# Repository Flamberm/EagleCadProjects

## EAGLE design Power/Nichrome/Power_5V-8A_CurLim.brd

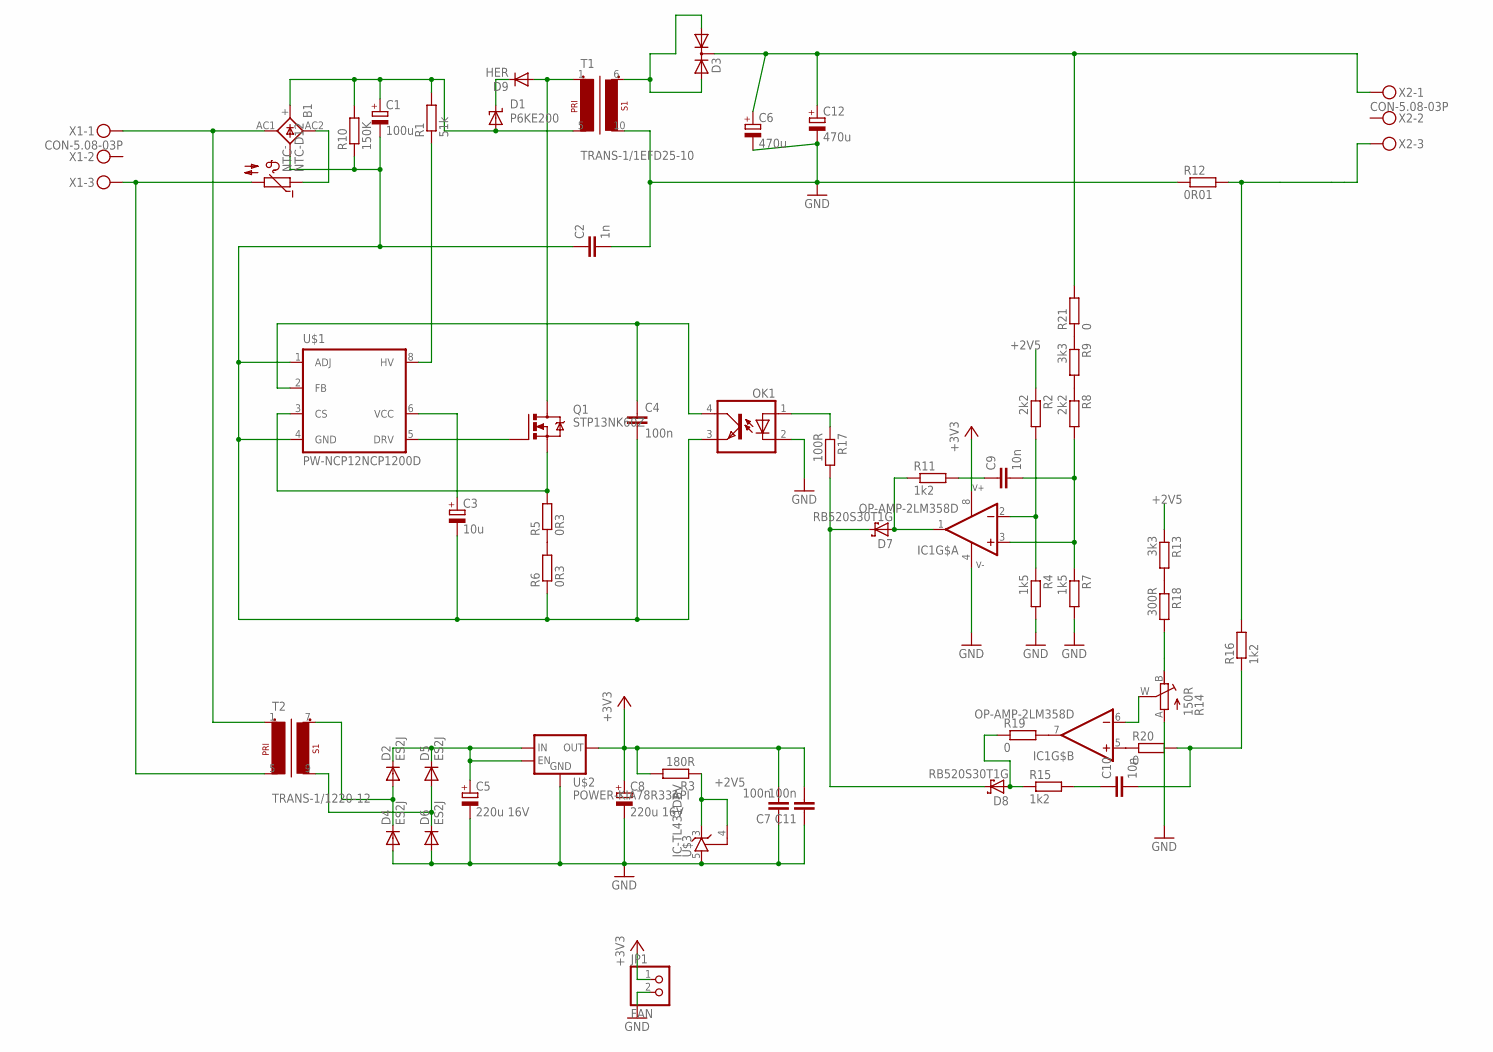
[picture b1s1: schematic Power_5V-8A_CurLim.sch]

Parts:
B1: RECTIFIERKBL; KBL
C1: 100u; C_D25-G10-CLAMP
C2: 1n; C050-024X044
C3: 10u; E5-5
C4, C7, C11: 100n; C0805
C5, C8: 220u 16V; E3,5-8
C6, C12: 470u; E5-10,5
C9, C10: 10n; C1206
D1: P6KE200; DO15-12
D2, D4, D5, D6: ES2J; DO214AC
D3: DIODE-DUAL-CCTO-220V; TO-220V
D7, D8: RB520S30T1G; SOD523
D9: HER; DO201-15
IC1: OP-AMP-2LM358D; SO8
JP1: FAN; 1X02
NTC: NTC-D12
OK1: OPTOTRANSPC817; DIL04
Q1: STP13NK60Z; TO-220V
R1: 51k; SQP-5
R2, R8: 2k2; R1206
R3: 180R; R1206
R4, R7: 1k5; R1206
R5, R6: 0R3; KNP-100B
R9, R13: 3k3; R1206
R10: 150K; MF-0125
R11, R15, R16: 1k2; R1206
R12: 0R01; R2512
R14: 150R; RJ9W
R17: 100R; R1206
R18: 300R; R1206
R19, R20, R21: 0; R0805
T1: TRANS-1/1EFD25-10; EFD25_10PIN
T2: TRANS-1/1220-12; 32.5-27.5-27.5
U$1: PW-NCP12NCP1200D; SO8
U$2: POWER-KIA78R33API; TO-220/4
U$3: IC-TL431DBV; SOT23-5L
X1, X2: CON-5.08-03P; MKDSN1,5/3-5,08

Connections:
+2V5: R2.1, R3.1, R13.1, U$3.3 (C), U$3.4 (R)
+3V3: C7.2, C8.+, C11.2, IC1.8 (V+), JP1.1, R3.2, U$2.O (OUT)
GND: C2.2, C5.-, C6.-, C7.1, C8.-, C11.1, C12.-, D4.A, D6.A, IC1.4 (V-), JP1.2, OK1.2 (C), R4.2, R7.2, R12.1, R14.A, T1.10 (S1-2), U$2.G (GND), U$3.5 (A)
unnamed: NTC.2, T2.5 (P1-2), X1.3
unnamed: B1.AC1 (AC2), T2.1 (P1-1), X1.1
unnamed: B1.AC2 (AC1), NTC.1
unnamed: R5.1, R6.2
unnamed: B1.-, C1.-, C2.1, C3.-, C4.2, OK1.3 (EMIT), R6.1, R10.1, U$1.1 (ADJ), U$1.4 (GND)
unnamed: B1.+, C1.+, D1.A, R1.2, R10.2, T1.5 (P1-2)
unnamed: D1.C, D9.C
unnamed: D9.A, Q1.2 (D), T1.1 (P1-1)
unnamed: IC1.2 (-IN), R2.2, R4.1
unnamed: R1.1, U$1.8 (HV)
unnamed: Q1.1 (G), U$1.5 (DRV)
unnamed: Q1.3 (S), R5.2, U$1.3 (CS)
unnamed: R8.1, R9.2
unnamed: C3.+, U$1.6 (VCC)
unnamed: C4.1, OK1.4 (COL), U$1.2 (FB)
unnamed: D3.1 (A1), D3.3 (A2), T1.6 (S1-1)
unnamed: C6.+, C12.+, D3.2 (C), R21.2, X2.1
unnamed: D2.A, D4.C, T2.7 (S1-1)
unnamed: D5.A, D6.C, T2.9 (S1-2)
unnamed: C9.2, IC1.3 (+IN), R7.1, R8.2
unnamed: D7.A, IC1.1 (OUT), R11.1
unnamed: C5.+, D2.C, D5.C, U$2.E (EN), U$2.I (IN)
unnamed: C9.1, R11.2
unnamed: IC1.6 (-IN), R14.W (S)
unnamed: D8.A, R15.1, R19.1
unnamed: C10.1, R15.2
unnamed: C10.2, R16.1, R20.2
unnamed: R12.2, R16.2, X2.3
unnamed: OK1.1 (A), R17.1
unnamed: R13.2, R18.1
unnamed: D7.C, D8.C, R17.2
unnamed: R14.B (E), R18.2
unnamed: IC1.7 (OUT), R19.2
unnamed: IC1.5 (+IN), R20.1
unnamed: R9.1, R21.1

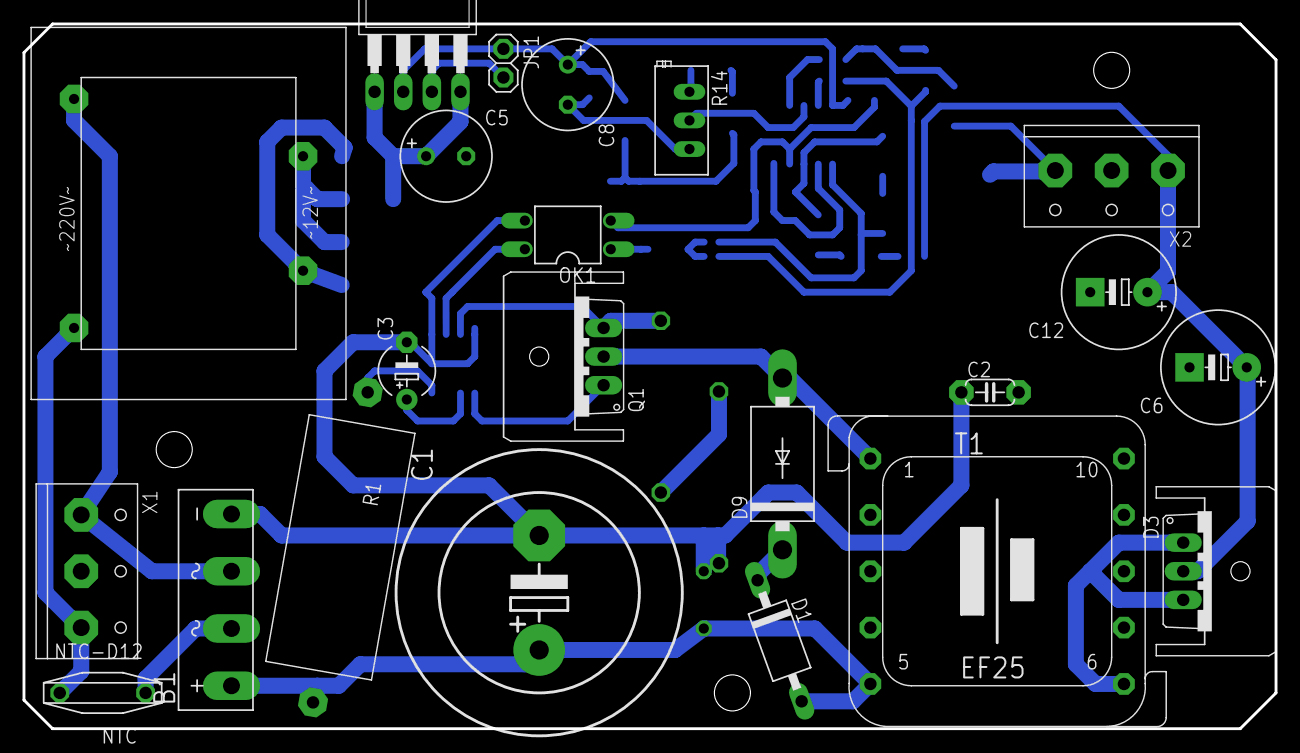
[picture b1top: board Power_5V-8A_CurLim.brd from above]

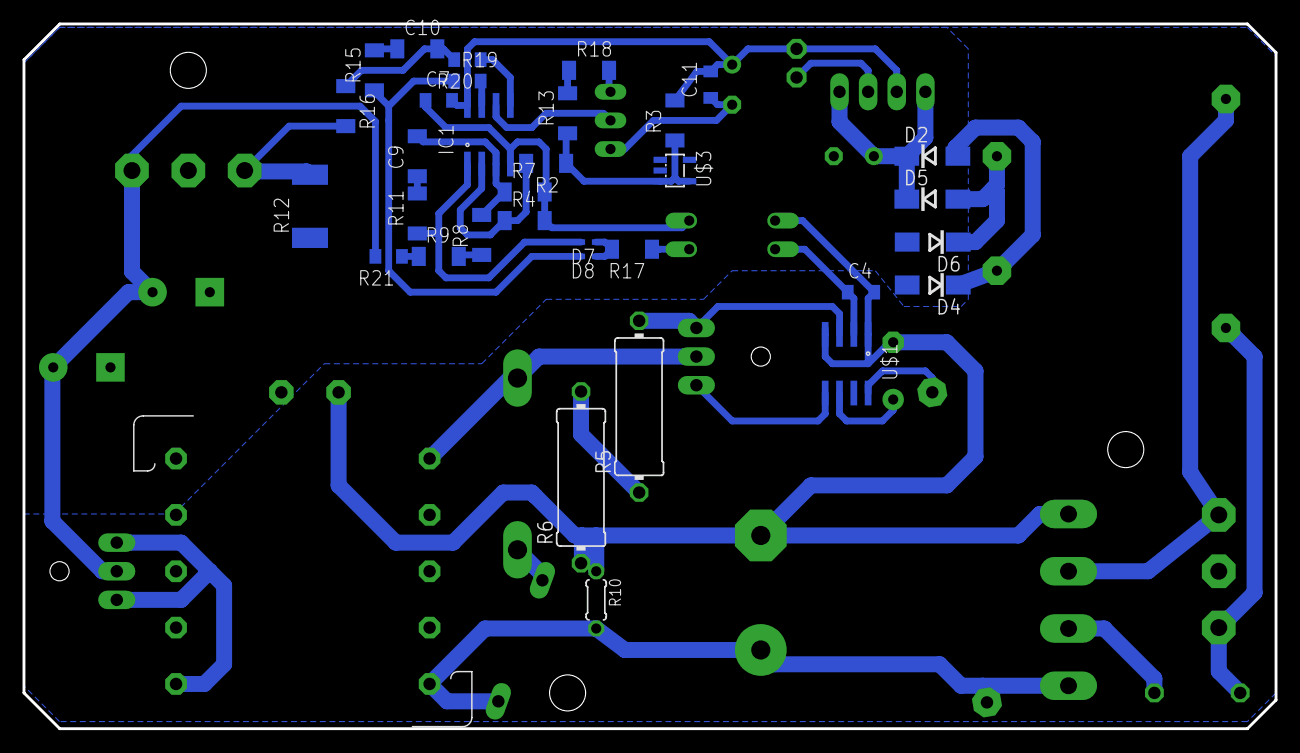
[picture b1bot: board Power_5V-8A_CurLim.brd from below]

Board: 2 copper layers, 111.1 x 62.5 mm, 57 parts (33 on the bottom side), 38 nets.

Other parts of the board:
U$4, U$5: SK95-3M3_HOLE

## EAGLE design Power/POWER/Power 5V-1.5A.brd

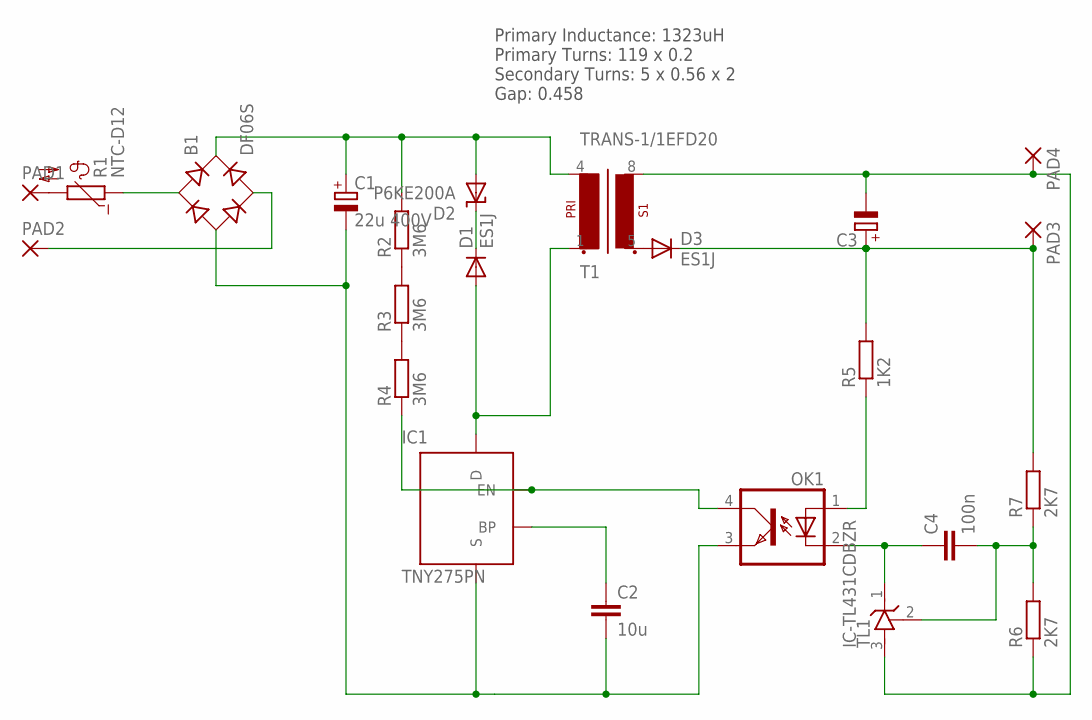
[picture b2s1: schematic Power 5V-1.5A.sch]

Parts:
B1: DF06S; DFS
C1: 22u 400V; E5-13
C2: 10u; C1210
C3: CPOL-EUE7.5-18; E7,5-18
C4: 100n; C0805
D1, D3: ES1J; DO214AC
D2: P6KE200A; DO15-12
IC1: TNY275PN; DIP-8C
OK1: OPTOTRANSPC817; DIL04
PAD1, PAD2, PAD3, PAD4: SMD5; SMD2,54-5,08
R1: NTC-D12
R2, R3, R4: 3M6; R0805
R5: 1K2; R1206
R6, R7: 2K7; R1206
T1: TRANS-1/1EFD20; EFD20_8PIN
TL1: IC-TL431CDBZR; SOT23

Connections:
unnamed: PAD1.1, R1.2
unnamed: B1.AC1, R1.1
unnamed: B1.AC2, PAD2.1
unnamed: B1.+, C1.+, D2.A, R2.2, T1.4 (P1-2)
unnamed: B1.-, C1.-, C2.2, IC1.5 (S), IC1.6 (S), IC1.7 (S), IC1.8 (S), OK1.3 (EMIT)
unnamed: C2.1, IC1.2 (BP)
unnamed: D1.A, IC1.4 (D), T1.1 (P1-1)
unnamed: D1.C, D2.C
unnamed: IC1.1 (EN), OK1.4 (COL), R4.1
unnamed: R2.1, R3.2
unnamed: R3.1, R4.2
unnamed: D3.A, T1.5 (S1-1)
unnamed: C3.+, D3.C, PAD3.1, R5.2, R7.2
unnamed: C3.-, PAD4.1, R6.1, T1.8 (S1-2), TL1.3 (A)
unnamed: OK1.1 (A), R5.1
unnamed: C4.1, OK1.2 (C), TL1.1 (C)
unnamed: C4.2, R6.2, R7.1, TL1.2 (R)

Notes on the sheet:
Primary Inductance: 1323uH Primary Turns: 119 x 0.2 Secondary Turns: 5 x 0.56 x 2 Gap: 0.458

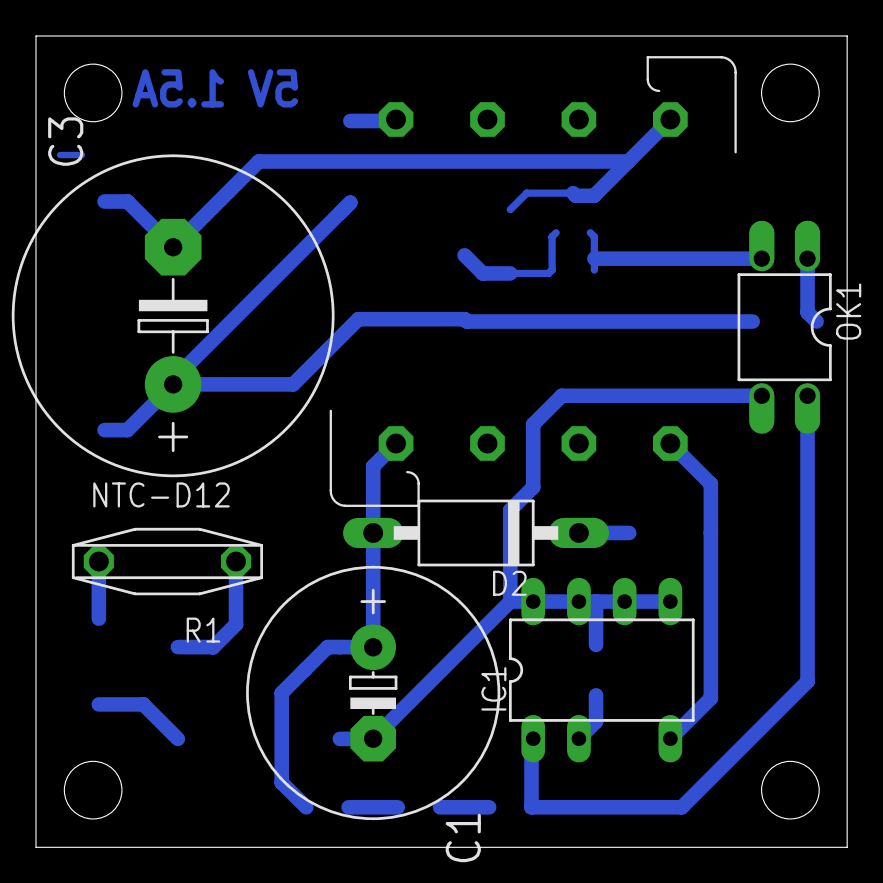
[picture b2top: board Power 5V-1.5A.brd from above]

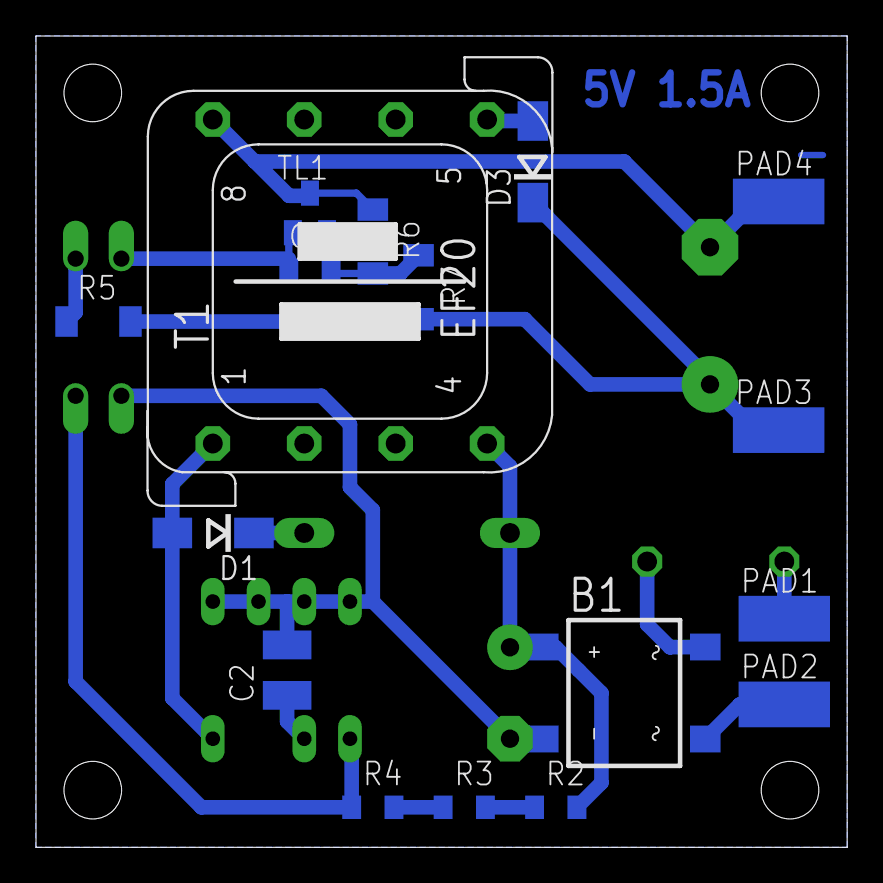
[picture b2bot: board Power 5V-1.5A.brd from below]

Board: 2 copper layers, 45.1 x 45.1 mm, 23 parts (17 on the bottom side), 17 nets.

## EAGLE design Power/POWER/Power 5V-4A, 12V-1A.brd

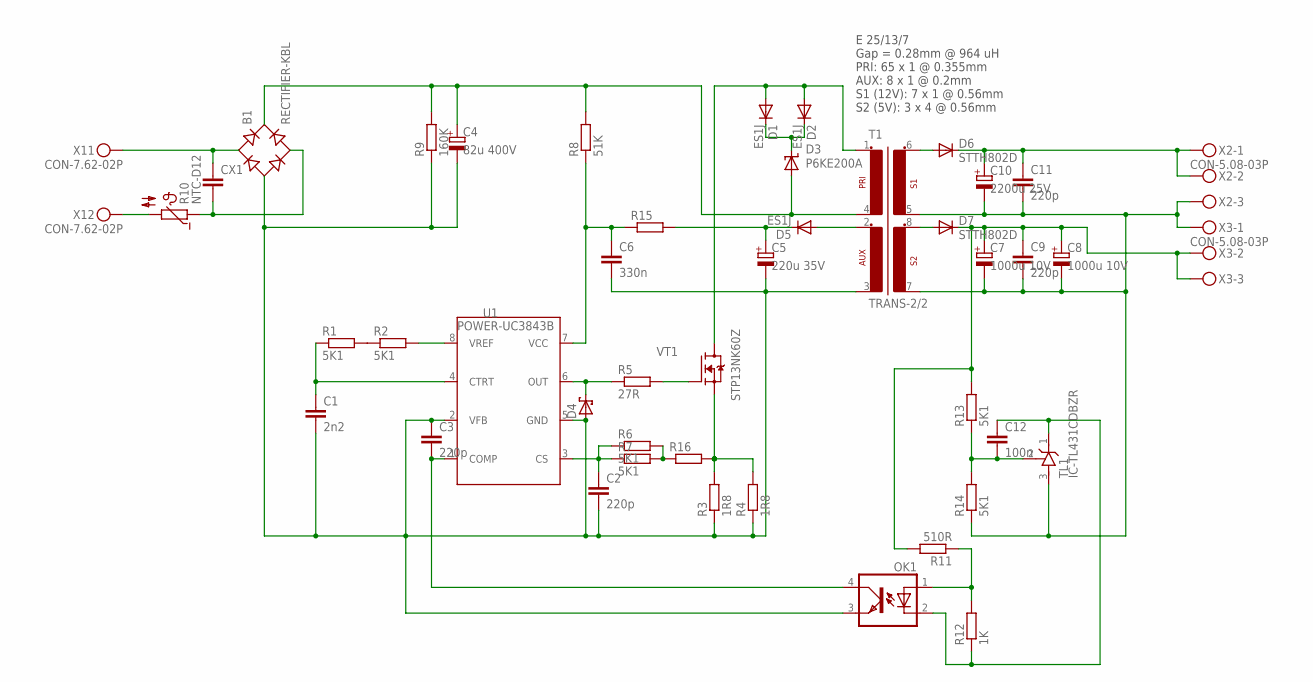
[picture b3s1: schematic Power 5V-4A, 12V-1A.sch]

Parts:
B1: RECTIFIER-KBL; KBL
C1: 2n2; CAP0603
C2, C3, C9, C11: 220p; CAP1206
C4: 82u 400V; C_D25-G10-CLAMP
C5: 220u 35V; E3,5-8
C6: 330n; CAP1206
C7, C8: 1000u 10V; E5-10,5
C10: 2200u 25V; E5-10,5
C12: 100n; CAP0805
CX1: CXXC15B6; XC15B6
D1, D2, D5: ES1J; DO214AC
D3: P6KE200A; DO15-12
D4: DIODE-SH_SMA; DO214AC
D6, D7: STTH802D; TO220ACS
OK1: OPTOTRANSPC817; DIL04
R1, R2, R6, R7, R13, R14: 5K1; RESC1508X50
R3, R4: 1R8; MF-025
R5: 27R; RESC3216X60
R8: 51K; MF-1
R9: 160K; MF-0125
R10: NTC-D12
R11: 510R; RESC2012X50
R12: 1K; RESC2012X50
R15, R16: R_R0805; RESC2012X50
T1: TRANS-2/2; EE25_8PIN_HORIZ
TL1: IC-TL431CDBZR; SOT95P240X115-3
U1: POWER-UC3843B; DIP-8
VT1: STP13NK60Z; TO-220V
X1: CON-7.62-02P; KF25C-7.62-02P-13
X2, X3: CON-5.08-03P; MKDSN1,5/3-5,08

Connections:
unnamed: R1.2, R2.1
unnamed: C1.1, R1.1, U1.4 (CTRT)
unnamed: B1.-, C1.2, C2.2, C3.1, C4.-, C5.-, C6.2, D4.A, OK1.3 (EMIT), R3.1, R4.1, R9.1, T1.3 (AUX-2), U1.2 (VFB), U1.5 (GND)
unnamed: R3.2, R4.2, R16.2, VT1.3 (S)
unnamed: D1.A, D2.A, T1.1 (P1-1), VT1.2 (D)
unnamed: B1.+, C4.+, D3.A, R8.2, R9.2, T1.4 (P1-2)
unnamed: D1.C, D2.C, D3.C
unnamed: D4.C, R5.1, U1.6 (OUT)
unnamed: R5.2, VT1.1 (G)
unnamed: C2.1, R6.1, R7.1, U1.3 (CS)
unnamed: C3.2, OK1.4 (COL), U1.1 (COMP)
unnamed: C6.1, R8.1, R15.1, U1.7 (VCC)
unnamed: B1.AC2, CX1.2, R10.1
unnamed: D5.A, T1.2 (AUX-1)
unnamed: B1.AC1, CX1.1, X1.P$1
unnamed: R10.2, X1.P$2
unnamed: D7.A, T1.8 (S2-1)
unnamed: C7.+, C8.+, C9.1, D7.C, R11.2, R13.2, X3.2, X3.3
unnamed: C5.+, D5.C, R15.2
unnamed: C7.-, C8.-, C9.2, C10.-, C11.2, R14.1, T1.5 (S1-2), T1.7 (S2-2), TL1.3 (A), X2.3, X3.1
unnamed: C10.+, C11.1, D6.C, X2.1, X2.2
unnamed: D6.A, T1.6 (S1-1)
unnamed: C12.1, OK1.2 (C), R12.1, TL1.1 (C)
unnamed: OK1.1 (A), R11.1, R12.2
unnamed: C12.2, R13.1, R14.2, TL1.2 (R)
unnamed: R6.2, R7.2, R16.1
VREF: R2.2, U1.8 (VREF)

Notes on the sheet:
E 25/13/7 Gap = 0.28mm @ 964 uH PRI: 65 x 1 @ 0.355mm AUX: 8 x 1 @ 0.2mm S1 (12V): 7 x 1 @ 0.56mm S2 (5V): 3 x 4 @ 0.56mm

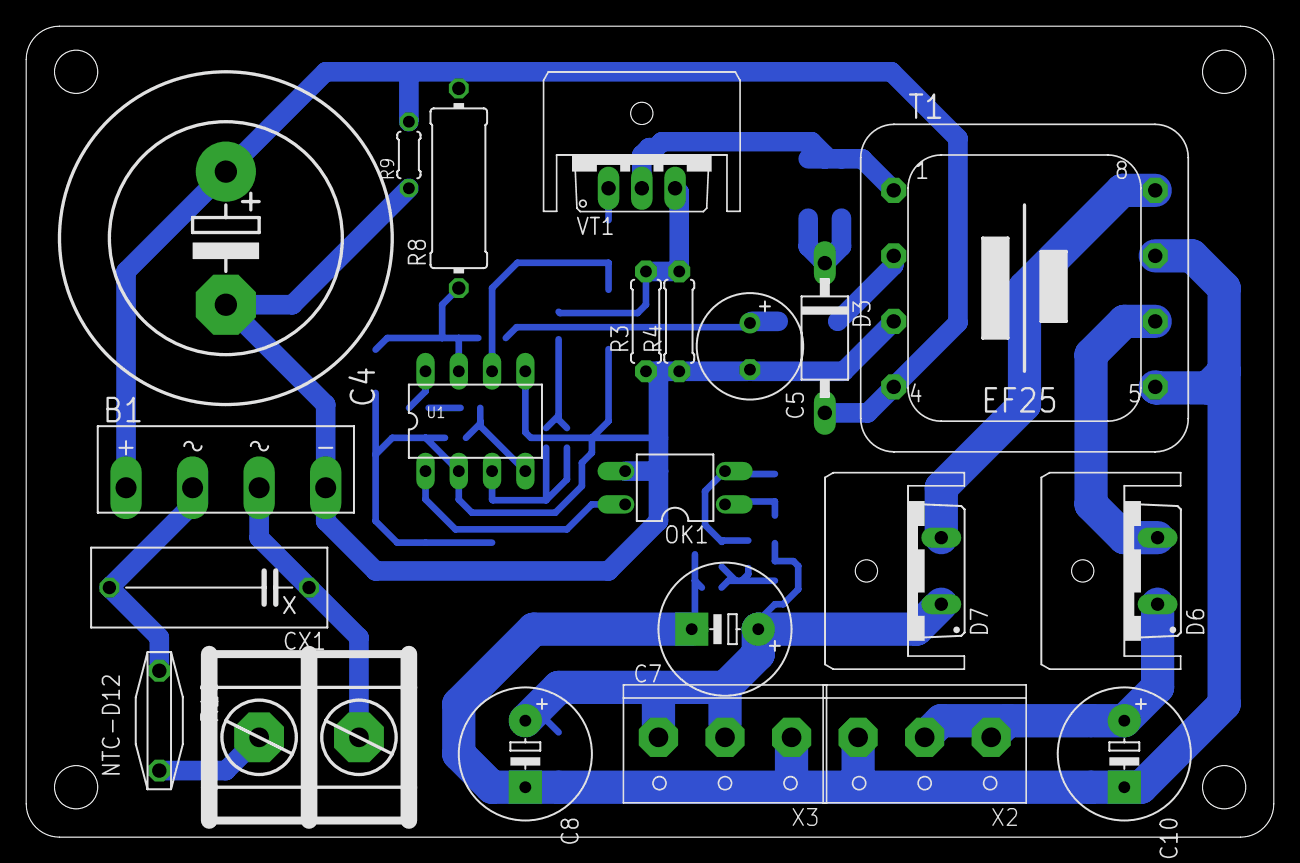
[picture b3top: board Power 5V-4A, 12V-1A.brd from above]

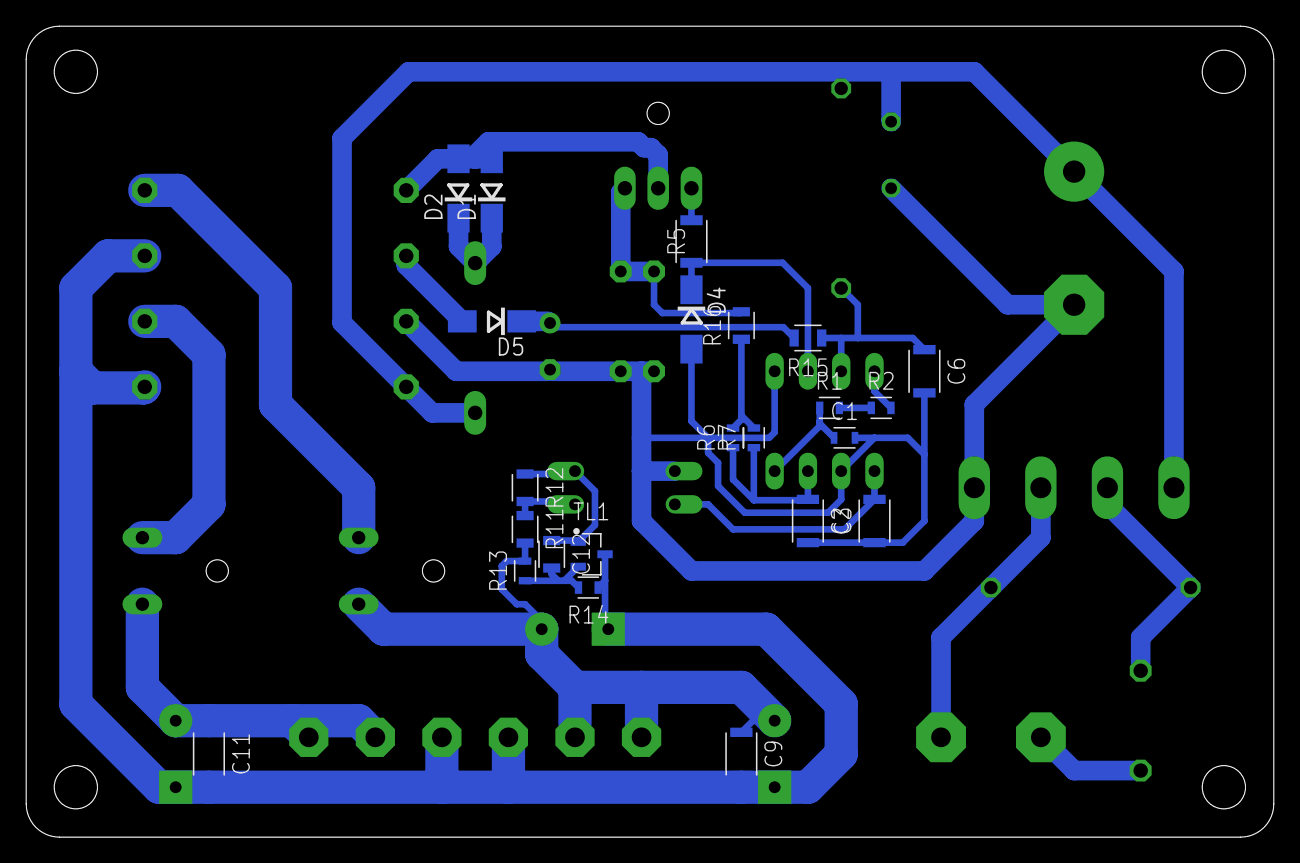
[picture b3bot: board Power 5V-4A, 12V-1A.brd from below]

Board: 2 copper layers, 95.2 x 61.9 mm, 48 parts (23 on the bottom side), 27 nets.

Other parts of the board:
U$1, U$2, U$3: SK95-3M3_HOLE

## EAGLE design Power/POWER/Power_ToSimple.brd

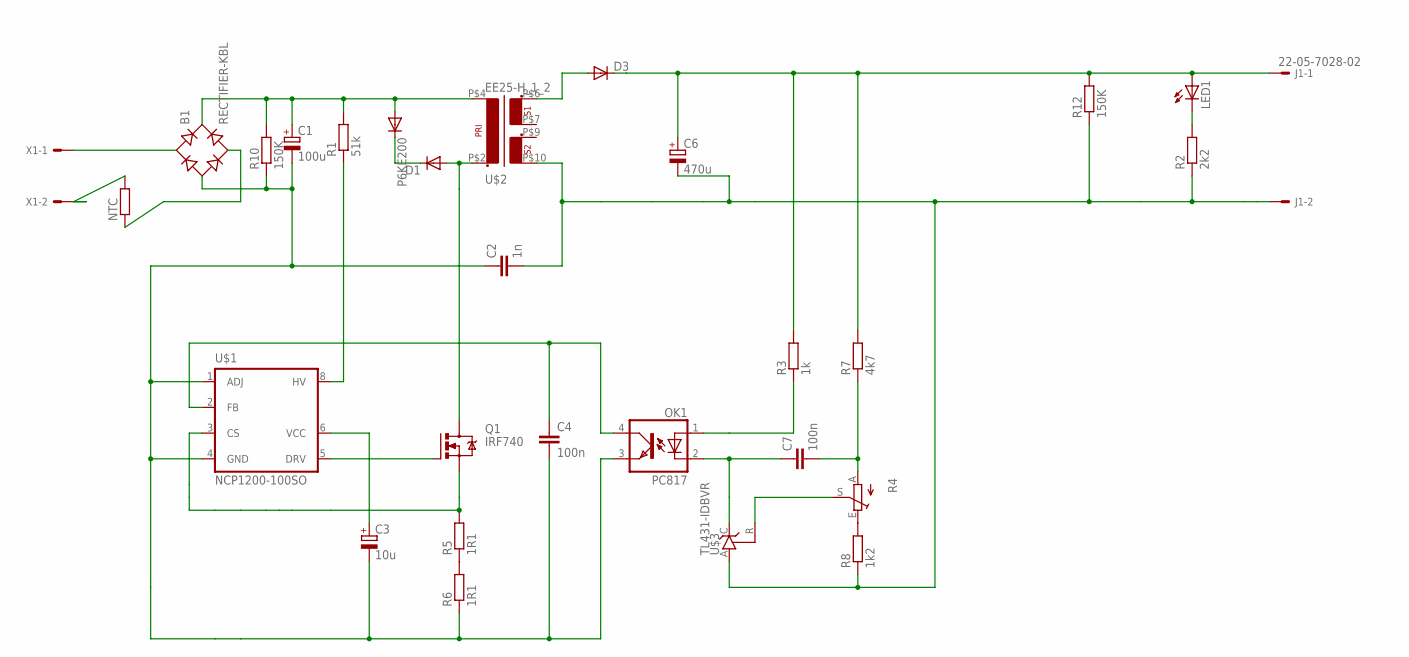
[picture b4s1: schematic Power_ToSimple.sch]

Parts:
B1: RECTIFIER-KBL; KBL
C1: 100u; EB22,5D
C2: 1n; C050-024X044
C3: 10u; E2,5-5
C4, C7: 100n; C1206
C6: 470u; E5-10,5
D1, D3: DIODE-DO-214AC; DO-214AC
J1: 22-05-7028-02; 7395-02
LED1: LED5MM
NTC: R-EU_0207/10; 0207/10
OK1: PC817; DIL04
P6KE200: DIODE-DO15-12; DO15-12
Q1: IRF740; TO220BV
R1: 51k; 0922/22
R2: 2k2; R1206
R3: 1k; R1206
R4: TRIM_EU-S75H; S75H
R5, R6: 1R1; R1206
R7: 4k7; R1206
R8: 1k2; R1206
R10, R12: 150K; R1206
U$1: NCP1200-100SO; SOP8
U$2: EE25-H_1_2; EE25
U$3: TL431-IDBVR; SOT23-5
X1: KK-156-2

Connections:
unnamed: NTC.2, X1.2
unnamed: B1.AC1, X1.1
unnamed: B1.AC2, NTC.1
unnamed: R5.1, R6.2
unnamed: B1.-, C1.-, C2.1, C3.-, C4.2, OK1.3 (EMIT), R6.1, R10.1, U$1.1 (ADJ), U$1.4 (GND)
unnamed: B1.+, C1.+, P6KE200.A, R1.2, R10.2, U$2.P$4 (2)
unnamed: D1.C, P6KE200.C
unnamed: D1.A, Q1.D, U$2.P$2 (1)
unnamed: C2.2, C6.-, J1.2, R2.1, R8.1, R12.1, U$2.P$10 (6), U$3.A
unnamed: R1.1, U$1.8 (HV)
unnamed: Q1.G, U$1.5 (DRV)
unnamed: Q1.S, R5.2, U$1.3 (CS)
unnamed: LED1.K (C), R2.2
unnamed: C3.+, U$1.6 (VCC)
unnamed: C4.1, OK1.4 (COL), U$1.2 (FB)
unnamed: D3.A, U$2.P$6 (3)
unnamed: C6.+, D3.C, J1.1, LED1.A, R3.2, R7.2, R12.2
unnamed: R4.S, U$3.R
unnamed: OK1.1 (A), R3.1
unnamed: C7.1, OK1.2 (C), U$3.C
unnamed: C7.2, R4.A, R7.1
unnamed: R4.E, R8.2

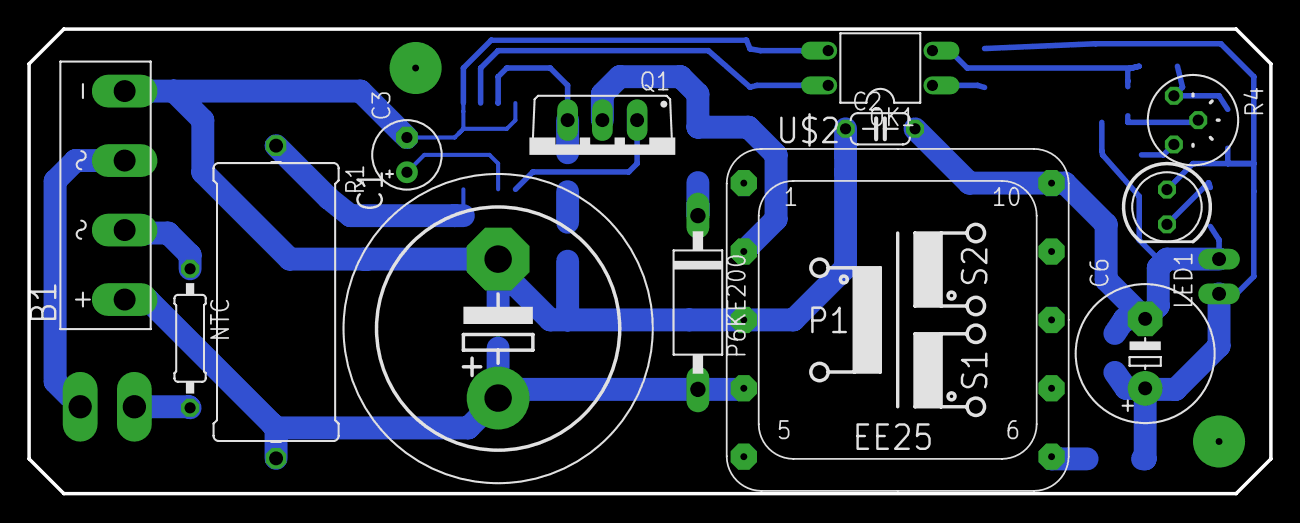
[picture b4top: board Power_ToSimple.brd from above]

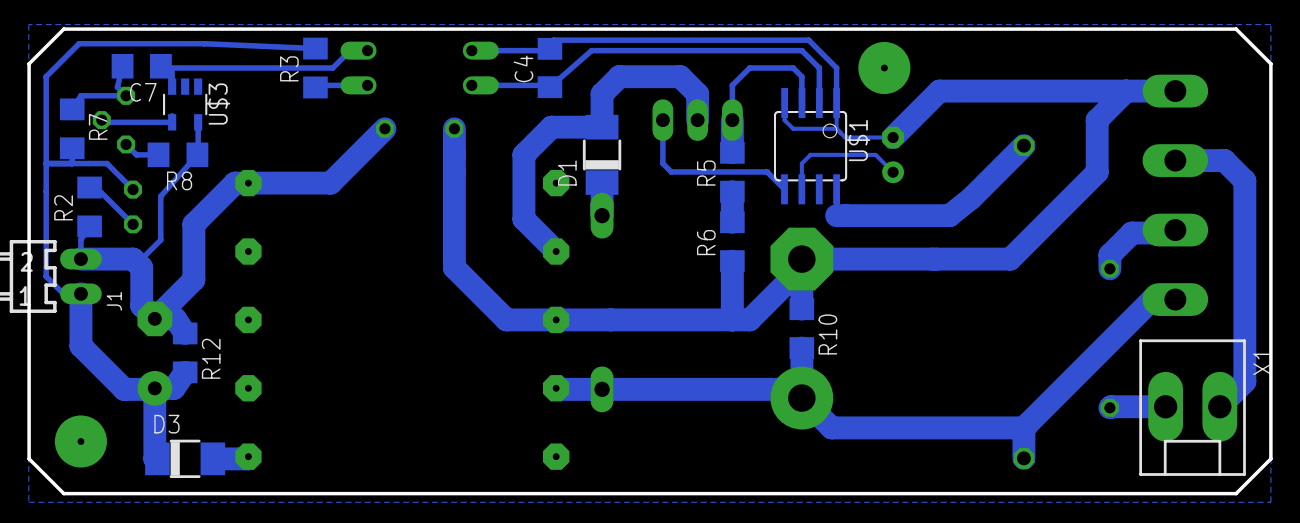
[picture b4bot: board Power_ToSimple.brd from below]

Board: 2 copper layers, 90.8 x 34.0 mm, 29 parts (16 on the bottom side), 22 nets.

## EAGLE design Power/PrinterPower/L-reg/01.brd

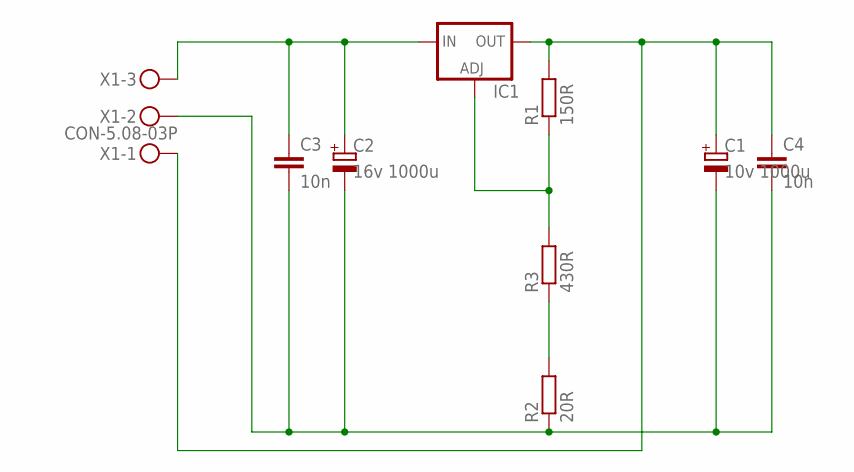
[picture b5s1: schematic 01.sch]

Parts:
C1: 10v 1000u; E5-10,5
C2: 16v 1000u; E5-10,5
C3, C4: 10n; C1206
IC1: LM350T; 317TS
R1: 150R; R1206
R2: 20R; R1206
R3: 430R; R0805
X1: CON-5.08-03P; MKDSN1,5/3-5,08

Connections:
unnamed: R2.2, R3.1
unnamed: IC1.1 (ADJ), R1.1, R3.2
unnamed: C1.+, C4.1, IC1.2 (OUT), R1.2, X1.1
unnamed: C1.-, C2.-, C3.2, C4.2, R2.1, X1.2
unnamed: C2.+, C3.1, IC1.3 (IN), X1.3

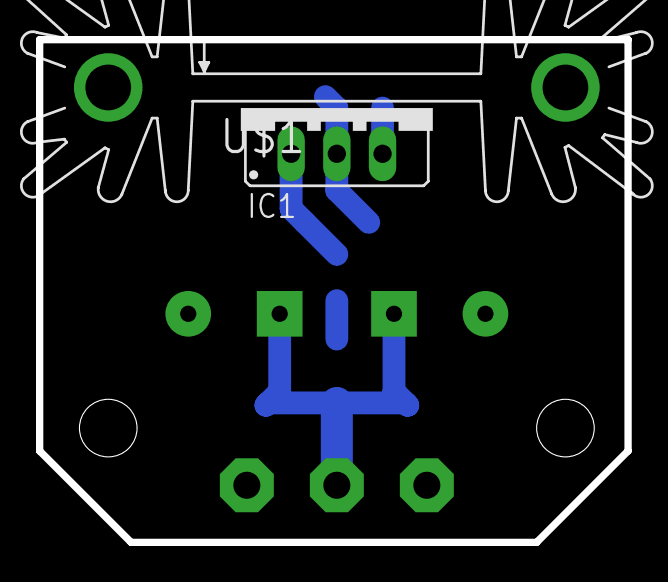
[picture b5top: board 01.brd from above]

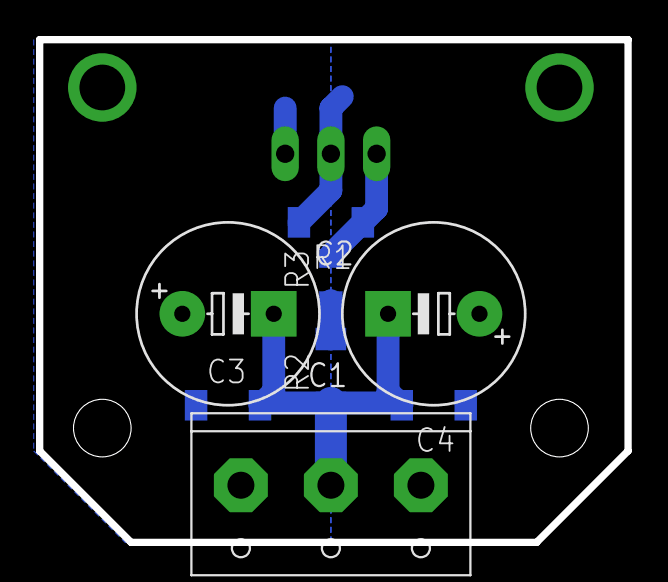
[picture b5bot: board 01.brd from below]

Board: 2 copper layers, 32.7 x 27.9 mm, 10 parts (8 on the bottom side), 5 nets.

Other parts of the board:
U$1: SK104-PAD
